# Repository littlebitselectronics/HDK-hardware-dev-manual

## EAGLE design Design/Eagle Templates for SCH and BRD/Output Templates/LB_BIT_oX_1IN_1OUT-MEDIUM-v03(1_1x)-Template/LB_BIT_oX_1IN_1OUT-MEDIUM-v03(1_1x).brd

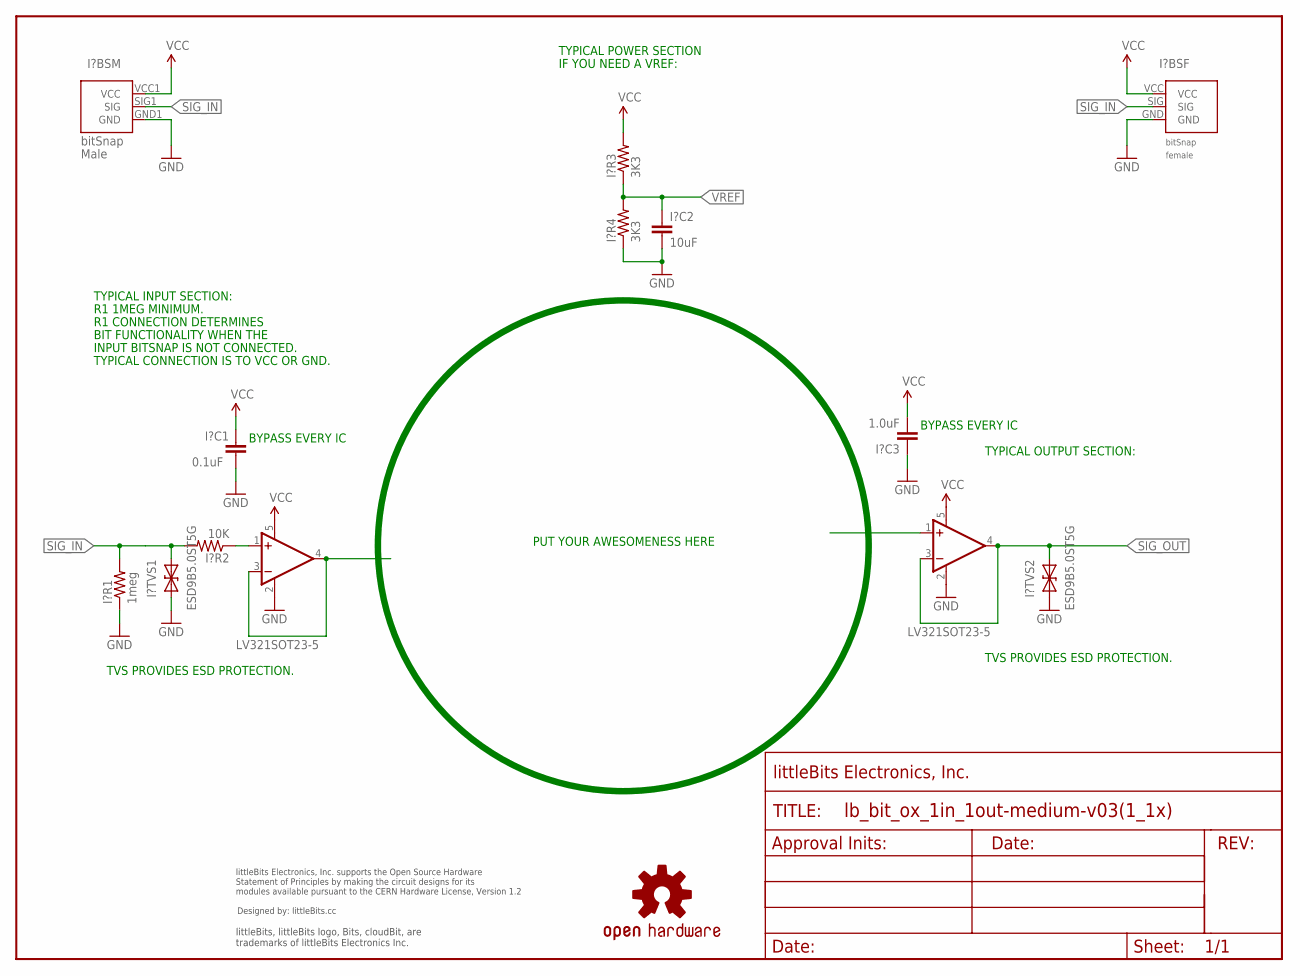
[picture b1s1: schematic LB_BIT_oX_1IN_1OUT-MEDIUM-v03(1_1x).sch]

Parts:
I?BSF: BITSNAP_V03_FEMALE
I?BSM: BITSNAP_V03_MALE
I?C1: 0.1uF; CAP-0603
I?C2: 10uF; CAP-0603
I?C3: 1.0uF; CAP-0603
I?R1: 1meg; RES-0603
I?R2: 10K; RES-0603
I?R3, I?R4: 3K3; RES-0603
I?TVS1, I?TVS2: ESD9B5.0ST5G; SOD-923
U1, U2: LV321SOT23-5; SOT23-5
U$1: FRAME-LETTER; FABDWG01-OHW
U$2: OSHWCREDIT
U$3: OSHW-LOGOL; OSHW-LOGO-L

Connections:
GND: I?BSF.GND, I?BSM.GND1 (GND), I?C1.2, I?C2.2, I?C3.1, I?R1.1, I?R4.1, I?TVS1.1 (A), I?TVS2.1 (A), U1.2 (V-), U2.2 (V-)
unnamed: U1.3 (-IN), U1.4 (OUT)
unnamed: I?R2.1, U1.1 (+IN)
SIG_IN: I?BSF.SIG, I?BSM.SIG1 (SIG), I?R1.2, I?R2.2, I?TVS1.2 (C)
SIG_OUT: I?TVS2.2 (C), U2.3 (-IN), U2.4 (OUT)
VCC: I?BSF.VCC, I?BSM.VCC1 (VCC), I?C1.1, I?C3.2, I?R3.2, U1.5 (V+), U2.5 (V+)
VREF: I?C2.1, I?R3.1, I?R4.2

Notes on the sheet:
R1 1MEG MINIMUM.
R1 CONNECTION DETERMINES
BIT FUNCTIONALITY WHEN THE
INPUT BITSNAP IS NOT CONNECTED.
TYPICAL CONNECTION IS TO VCC OR GND.
TVS PROVIDES ESD PROTECTION.
TYPICAL INPUT SECTION:
TYPICAL POWER SECTION
IF YOU NEED A VREF:
PUT YOUR AWESOMENESS HERE
BYPASS EVERY IC
TYPICAL OUTPUT SECTION:

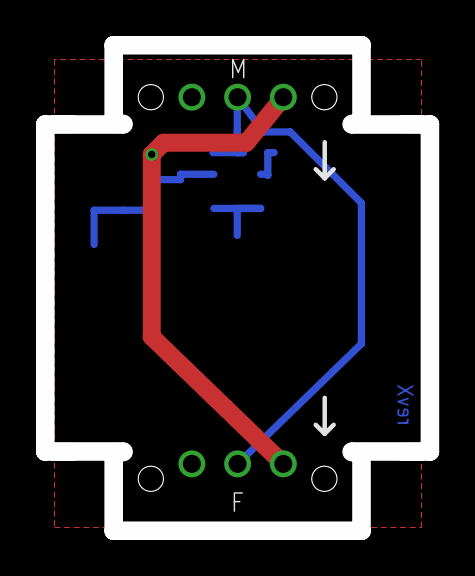
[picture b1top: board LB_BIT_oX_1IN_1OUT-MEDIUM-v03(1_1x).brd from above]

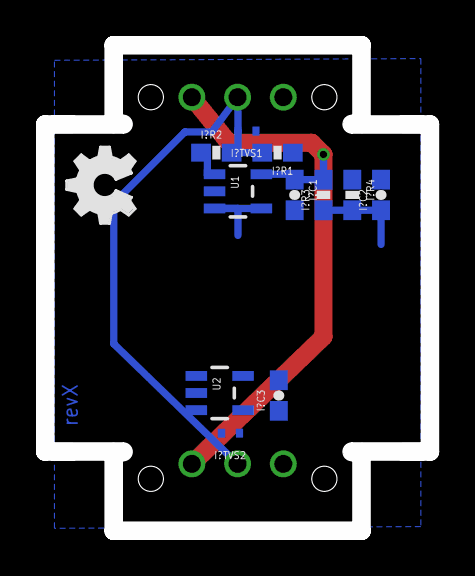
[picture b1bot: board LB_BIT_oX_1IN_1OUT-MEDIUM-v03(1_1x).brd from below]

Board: 2 copper layers, 20.4 x 26.0 mm, 17 parts (12 on the bottom side), 7 nets.

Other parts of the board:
U$4: OSHW_FILLX150_NOTEXT

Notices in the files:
parts and their libraries:
LITTLEBITS: modules available pursuant to the CERN Hardware License,
Version 1.2
LITTLEBITS: modules available pursuant to the CERN Hardware License, Version 1.2
